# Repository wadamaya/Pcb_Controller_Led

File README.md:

# Pcb_Controller_Led
PLaca controladora led con TTgo lora 32 V1.6

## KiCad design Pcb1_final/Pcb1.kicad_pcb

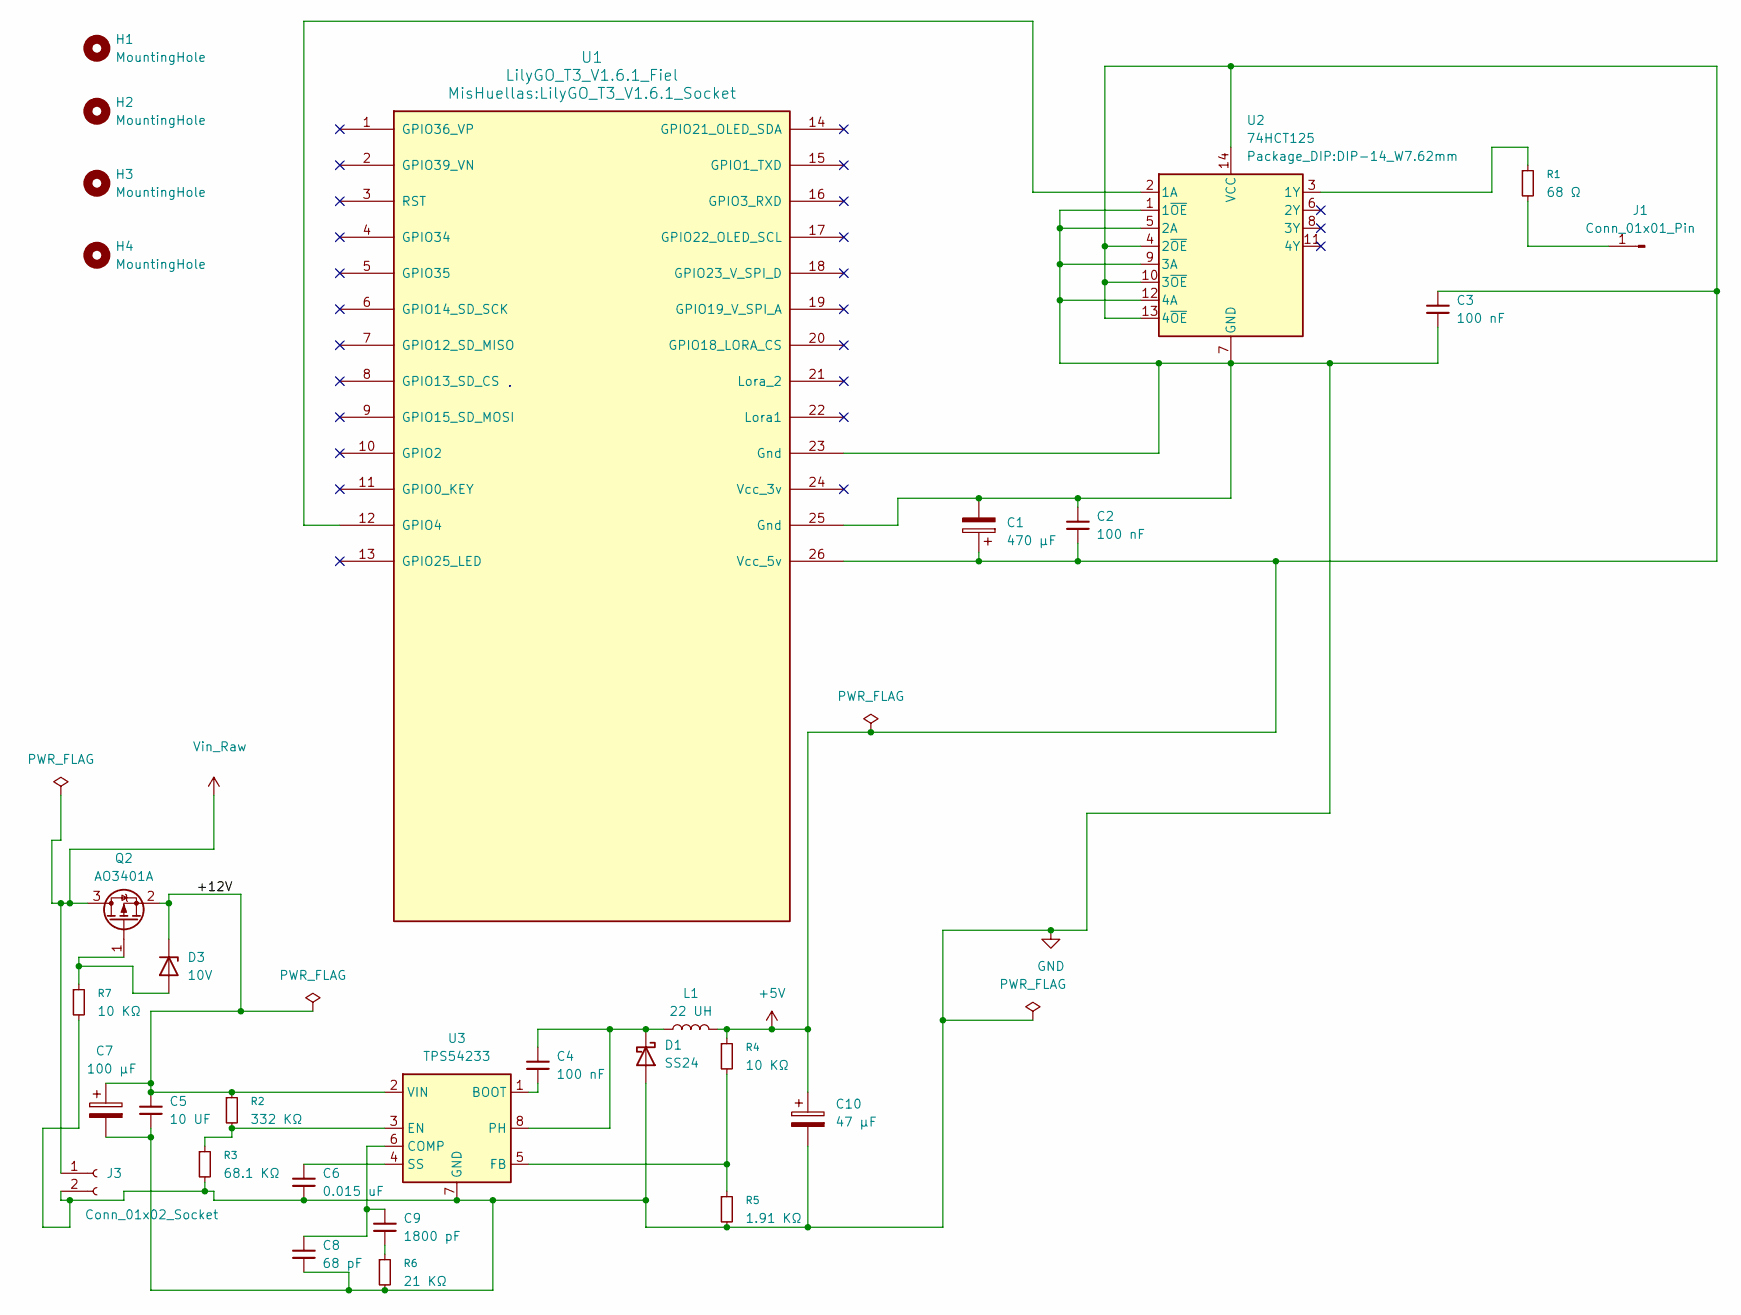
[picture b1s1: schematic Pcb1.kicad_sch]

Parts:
C1: 470 µF; CP_Radial_D8.0mm_P3.50mm
C2, C3, C4: 100 nF; C_Disc_D3.8mm_W2.6mm_P2.50mm
C5: 10 UF; C_Disc_D3.8mm_W2.6mm_P2.50mm
C6: 0.015 uF; C_Disc_D3.8mm_W2.6mm_P2.50mm
C7: 100 µF; CP_Radial_D8.0mm_P3.50mm
C8: 68 pF; C_Disc_D3.8mm_W2.6mm_P2.50mm
C9: 1800 pF; C_Disc_D3.8mm_W2.6mm_P2.50mm
C10: 47 µF; CP_Radial_D8.0mm_P3.50mm
D1: SS24; D_SMA
D3: 10V; D_SMA
H1, H2, H3, H4: MountingHole; MountingHole_3.2mm_M3
J1: Conn_01x01_Pin; PinHeader_1x01_P2.54mm_Vertical
J3: Conn_01x02_Socket; TerminalBlock_Phoenix_PT-1,5-2-5.0-H_1x02_P5.00mm_Horizontal
L1: 22 UH; L_Bourns_SRP5030T
Q2: AO3401A; SOT-23
R1: 68 Ω; R_Axial_DIN0207_L6.3mm_D2.5mm_P7.62mm_Horizontal
R2: 332 KΩ; R_Axial_DIN0207_L6.3mm_D2.5mm_P7.62mm_Horizontal
R3: 68.1 KΩ; R_Axial_DIN0207_L6.3mm_D2.5mm_P7.62mm_Horizontal
R4, R7: 10 KΩ; R_Axial_DIN0207_L6.3mm_D2.5mm_P7.62mm_Horizontal
R5: 1.91 KΩ; R_Axial_DIN0207_L6.3mm_D2.5mm_P7.62mm_Horizontal
R6: 21 KΩ; R_Axial_DIN0207_L6.3mm_D2.5mm_P7.62mm_Horizontal
U1: LilyGO_T3_V1.6.1_Fiel; LilyGO_T3_V1.6.1_Socket
U2: 74HCT125; DIP-14_W7.62mm
U3: TPS54233; SOIC-8_3.9x4.9mm_P1.27mm

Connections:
+5V: C1.1, C2.2, C3.1, C10.1, L1.2, R4.1, U1.26 (Vcc_5v), U2.4 (2~OE), U2.10 (3~OE), U2.13 (4~OE), U2.14 (VCC)
/+12V: C5.1, C7.1, D3.1 (K), Q2.2 (S), R2.1, U3.2 (VIN)
GND: C1.2, C2.1, C3.2, C5.2, C6.2, C7.2, C8.2, C10.2, D1.2 (A), J3.2, R3.2, R5.2, R6.2, R7.2, U1.23 (Gnd), U1.25 (Gnd), U2.1 (1~OE), U2.5 (2A), U2.7 (GND), U2.9 (3A), U2.12 (4A), U3.7 (GND)
unnamed: C9.2, R6.1
unnamed: C4.1, D1.1 (K), L1.1, U3.8 (PH)
unnamed: D3.2 (A), Q2.1 (G), R7.1
unnamed: J1.1 (Pin_1_1), R1.2
unnamed: U1.12 (GPIO4), U2.2 (1A)
unnamed: R1.1, U2.3 (1Y)
unnamed: C4.2, U3.1 (BOOT)
unnamed: C8.1, C9.1, U3.6 (COMP)
unnamed: R2.2, R3.1, U3.3 (EN)
unnamed: R4.2, R5.1, U3.5 (FB)
unnamed: C6.1, U3.4 (SS)
Vin_Raw: J3.1, Q2.3 (D)

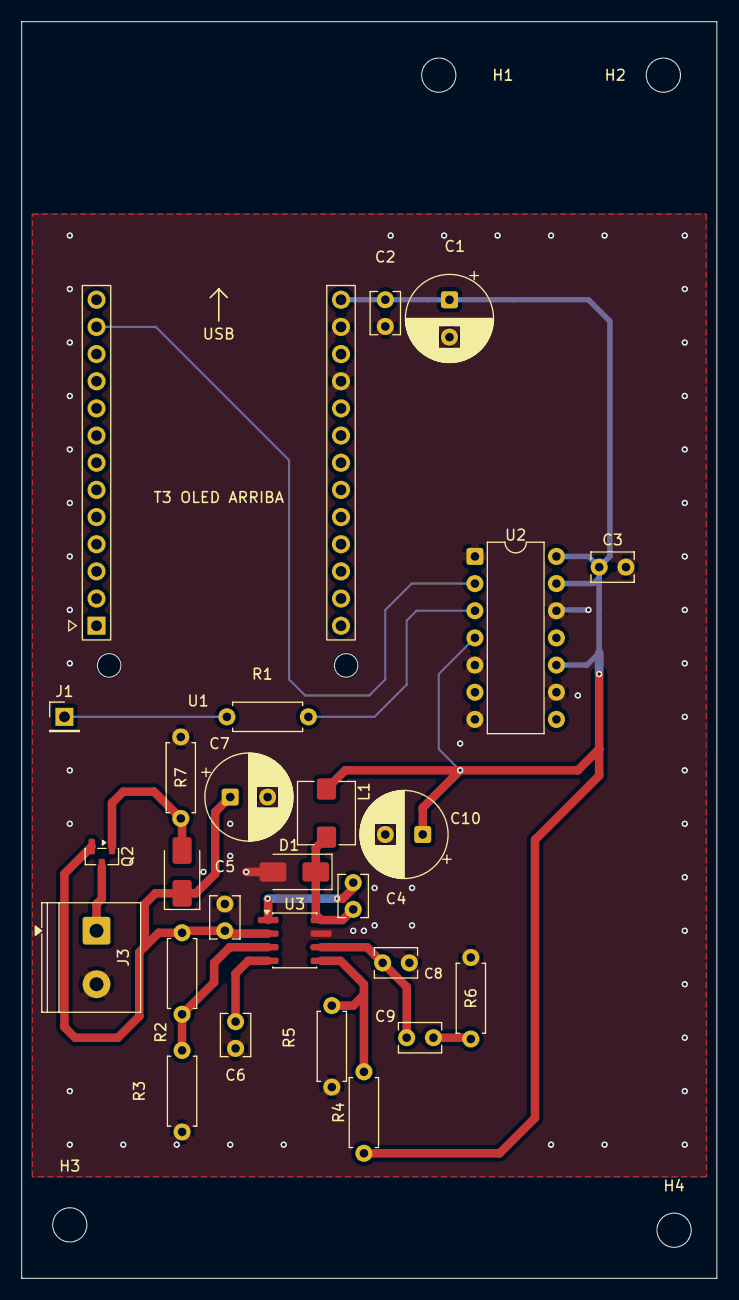
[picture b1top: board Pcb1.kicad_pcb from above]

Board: 2 copper layers, 65.0 x 117.5 mm, 30 parts (0 on the bottom side), 15 nets.
